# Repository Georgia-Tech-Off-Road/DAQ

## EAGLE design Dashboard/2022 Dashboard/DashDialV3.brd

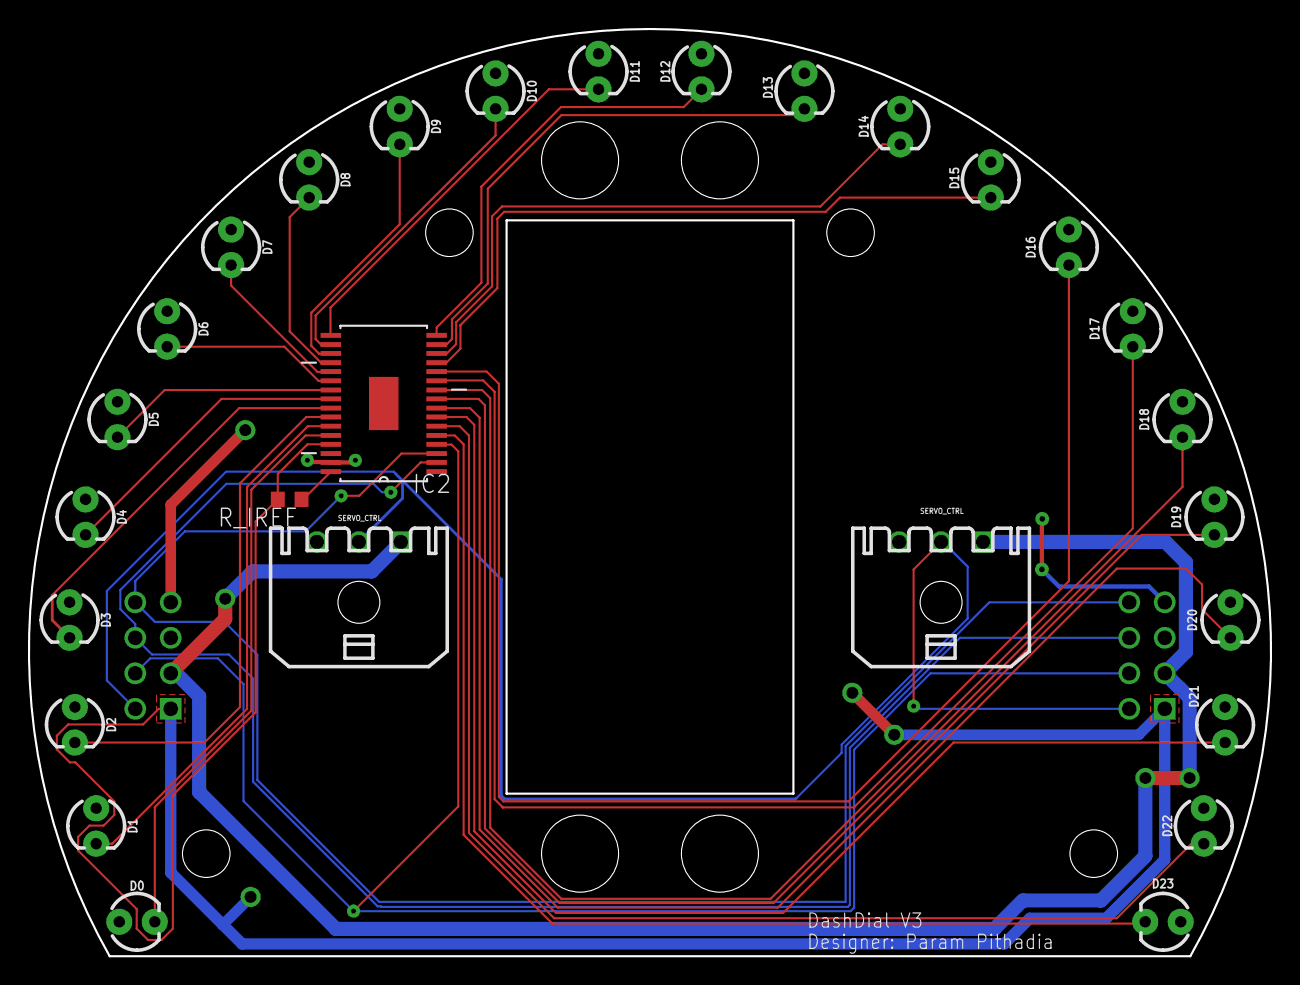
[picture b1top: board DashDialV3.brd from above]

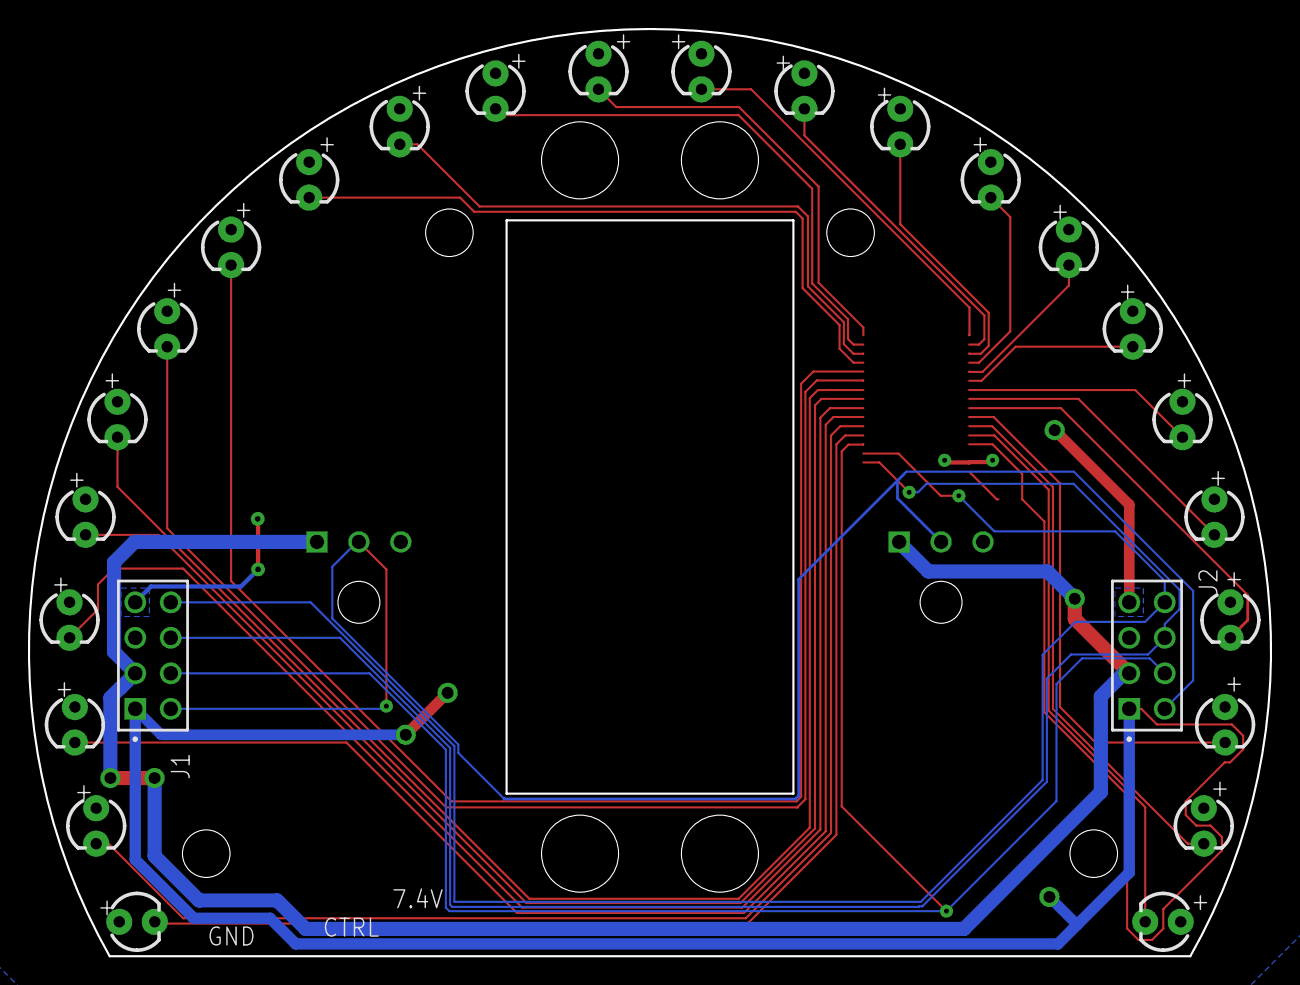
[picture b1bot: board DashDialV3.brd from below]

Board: 2 copper layers, 88.9 x 66.3 mm, 30 parts (2 on the bottom side), 32 nets.

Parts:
D0, D1, D2, D3, D4, D5, D6, D7, D8, D9, D10, D11, D12, D13, D14, D15, D16, D17, D18, D19, D20, D21, D22, D23: LED_3MM
IC2: TLC5952DAP; SOP65P810X120-33N
J1, J2: ESW-104-23-L-D; SAMTEC_ESW-104-23-L-D
R_IREF: 2.4k; R0603
SERVO, SERVO1: 43650-0300

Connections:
3.3V: D0.A, D1.A, D2.A, D3.A, D4.A, D5.A, D6.A, D7.A, D8.A, D9.A, D10.A, D11.A, D12.A, D13.A, D14.A, D15.A, D16.A, D17.A, D18.A, D19.A, D20.A, D21.A, D22.A, D23.A, IC2.31, J1.07, J2.07
7.4V: J1.03, J2.03, SERVO.P$1, SERVO1.P$1
GND: IC2.1, IC2.29, IC2.33, J1.01, J2.01, R_IREF.2, SERVO.P$3, SERVO1.P$3
LAT: IC2.4, J1.04, J2.04
unnamed: IC2.32, R_IREF.1
OUT0: D23.K, IC2.5
OUT1: D22.K, IC2.6
OUT2: D21.K, IC2.7
OUT3: D20.K, IC2.8
OUT4: D19.K, IC2.9
OUT5: D18.K, IC2.10
OUT6: D17.K, IC2.11
OUT7: D16.K, IC2.12
OUT8: D15.K, IC2.13
OUT9: D14.K, IC2.14
OUT10: D13.K, IC2.15
OUT11: D12.K, IC2.16
OUT12: D11.K, IC2.17
OUT13: D10.K, IC2.18
OUT14: D9.K, IC2.19
OUT15: D8.K, IC2.20
OUT16: D7.K, IC2.21
OUT17: D6.K, IC2.22
OUT18: D5.K, IC2.23
OUT19: D4.K, IC2.24
OUT20: D3.K, IC2.25
OUT21: D2.K, IC2.26
OUT22: D1.K, IC2.27
OUT23: D0.K, IC2.28
SCLK: IC2.3, J1.08, J2.08
SERVO_CTRL: J1.02, J2.02, SERVO.P$2, SERVO1.P$2
SIN: IC2.2, J1.06, J2.06

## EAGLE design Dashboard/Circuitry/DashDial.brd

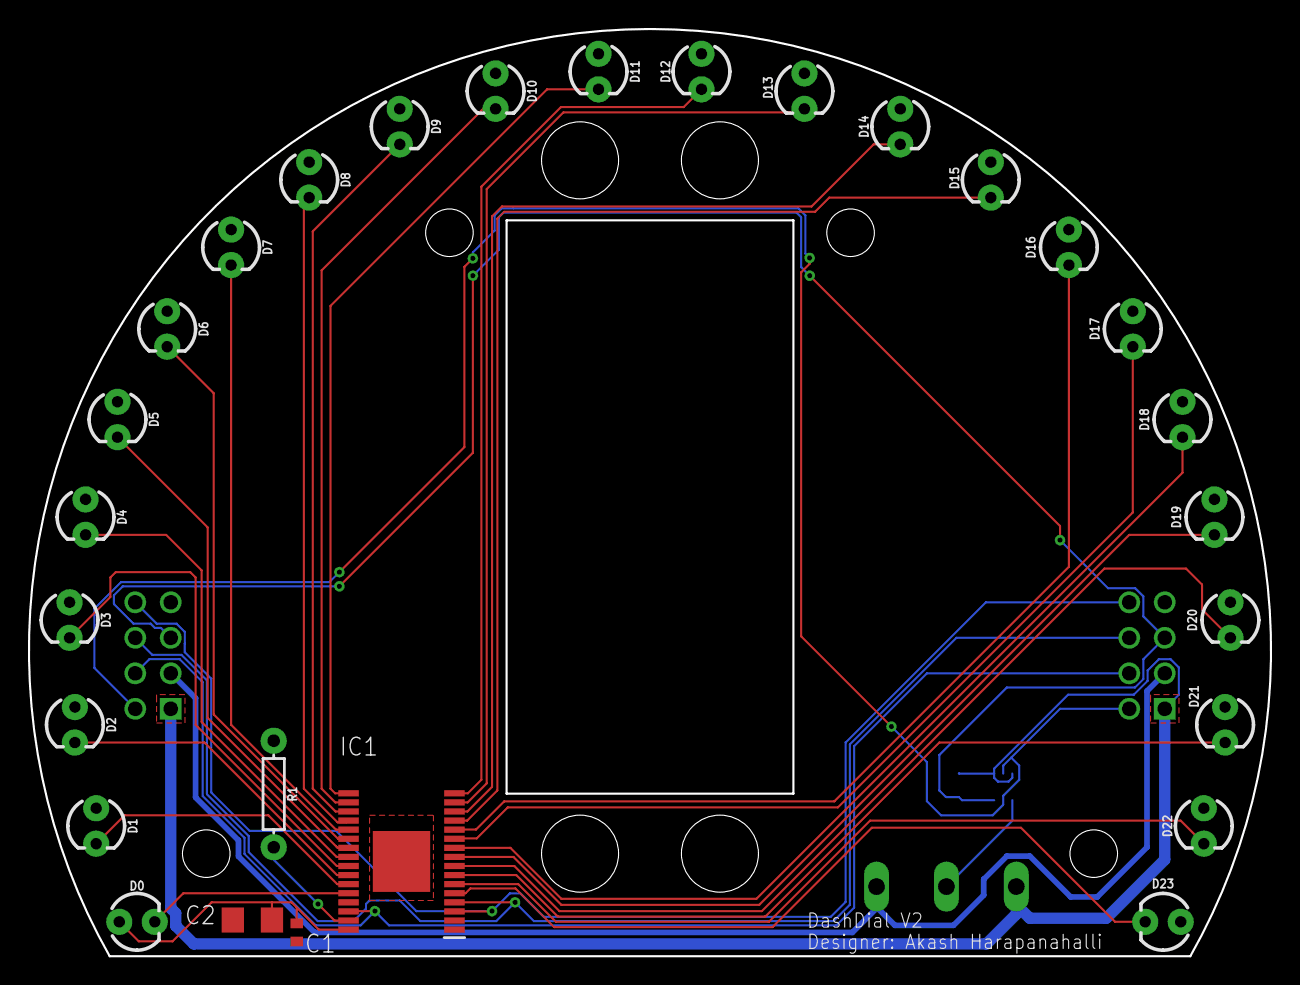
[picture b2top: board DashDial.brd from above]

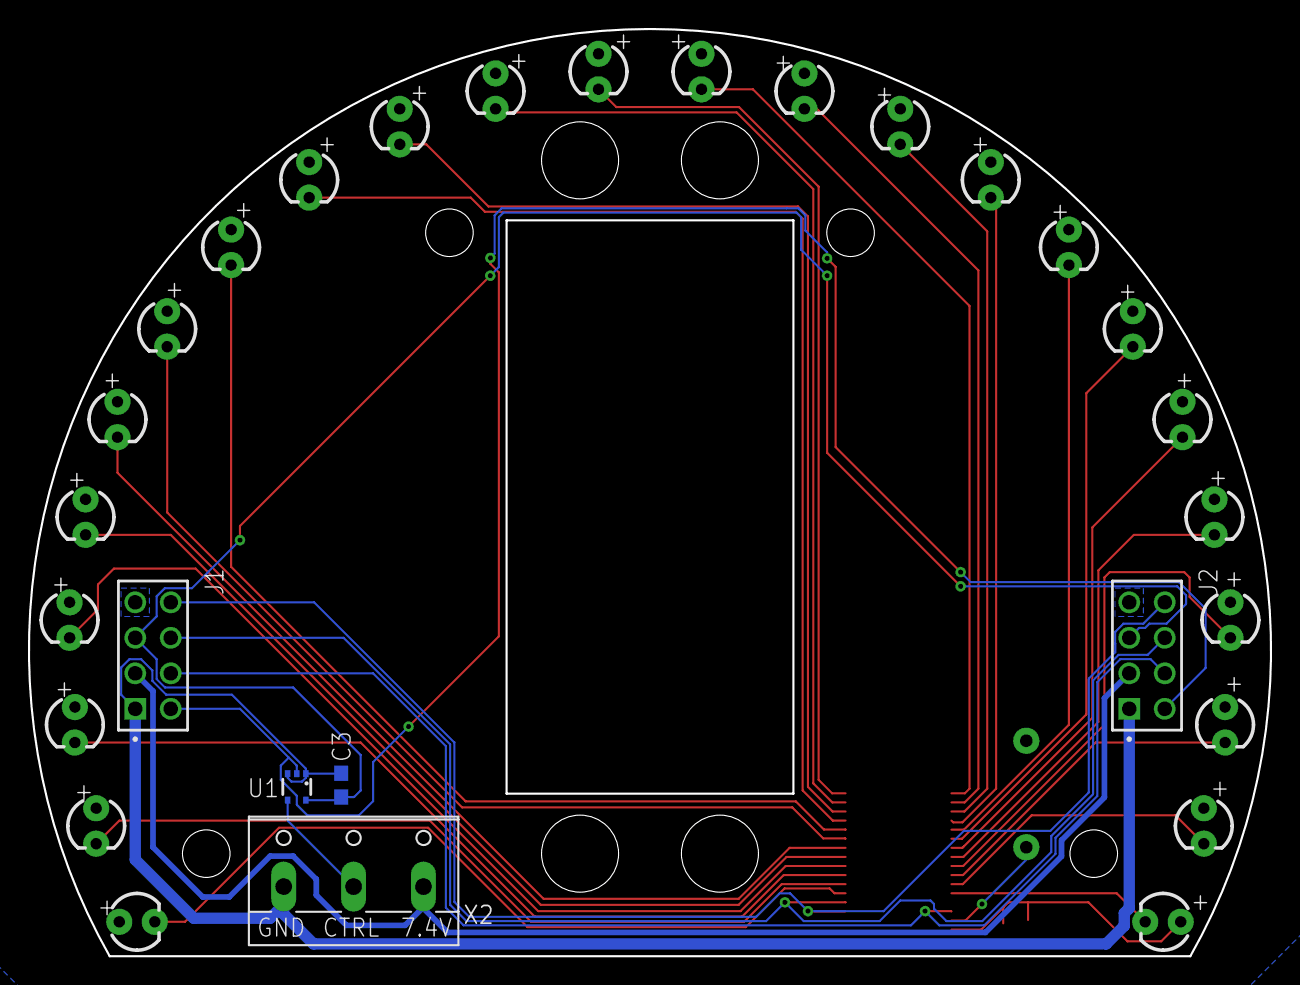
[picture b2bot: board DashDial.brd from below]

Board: 2 copper layers, 88.9 x 66.3 mm, 33 parts (5 on the bottom side), 34 nets.

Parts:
C1: 0.1uF; C0402
C2: 100uF; C1206
C3: 0.1uF; 0603
D0, D1, D2, D3, D4, D5, D6, D7, D8, D9, D10, D11, D12, D13, D14, D15, D16, D17, D18, D19, D20, D21, D22, D23: LED_3MM
IC1: TLC5947DAPR; SOP65P810X120-33N
J1, J2: ESW-104-23-L-D; SAMTEC_ESW-104-23-L-D
R1: 3k; AXIAL-0.3
U1: LOGIC SHIFTER; SOT353
X2: SERVO; W237-103

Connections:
3.3V: C1.2, C2.2, D0.A, D1.A, D2.A, D3.A, D4.A, D5.A, D6.A, D7.A, D8.A, D9.A, D10.A, D11.A, D12.A, D13.A, D14.A, D15.A, D16.A, D17.A, D18.A, D19.A, D20.A, D21.A, D22.A, D23.A, IC1.32, J1.07, J2.07
5V: C3.1, J1.05, J2.05, U1.5
7.4V: J1.03, J2.03, X2.3
GND: C1.1, C2.1, C3.2, IC1.1, IC1.2, IC1.33, J1.01, J2.01, R1.P$1, U1.1, U1.3, X2.1
LAT: IC1.30, J1.04, J2.04
unnamed: U1.4, X2.2
unnamed: IC1.31, R1.P$2
OUT0: D23.K, IC1.5
OUT1: D22.K, IC1.6
OUT2: D21.K, IC1.7
OUT3: D20.K, IC1.8
OUT4: D19.K, IC1.9
OUT5: D18.K, IC1.10
OUT6: D17.K, IC1.11
OUT7: D16.K, IC1.12
OUT8: D15.K, IC1.13
OUT9: D14.K, IC1.14
OUT10: D13.K, IC1.15
OUT11: D12.K, IC1.16
OUT12: D11.K, IC1.17
OUT13: D10.K, IC1.18
OUT14: D9.K, IC1.19
OUT15: D8.K, IC1.20
OUT16: D7.K, IC1.21
OUT17: D6.K, IC1.22
OUT18: D5.K, IC1.23
OUT19: D4.K, IC1.24
OUT20: D3.K, IC1.25
OUT21: D2.K, IC1.26
OUT22: D1.K, IC1.27
OUT23: D0.K, IC1.28
SCLK: IC1.3, J1.08, J2.08
SERVO_CTRL: J1.02, J2.02, U1.2
SIN: IC1.4, J1.06, J2.06

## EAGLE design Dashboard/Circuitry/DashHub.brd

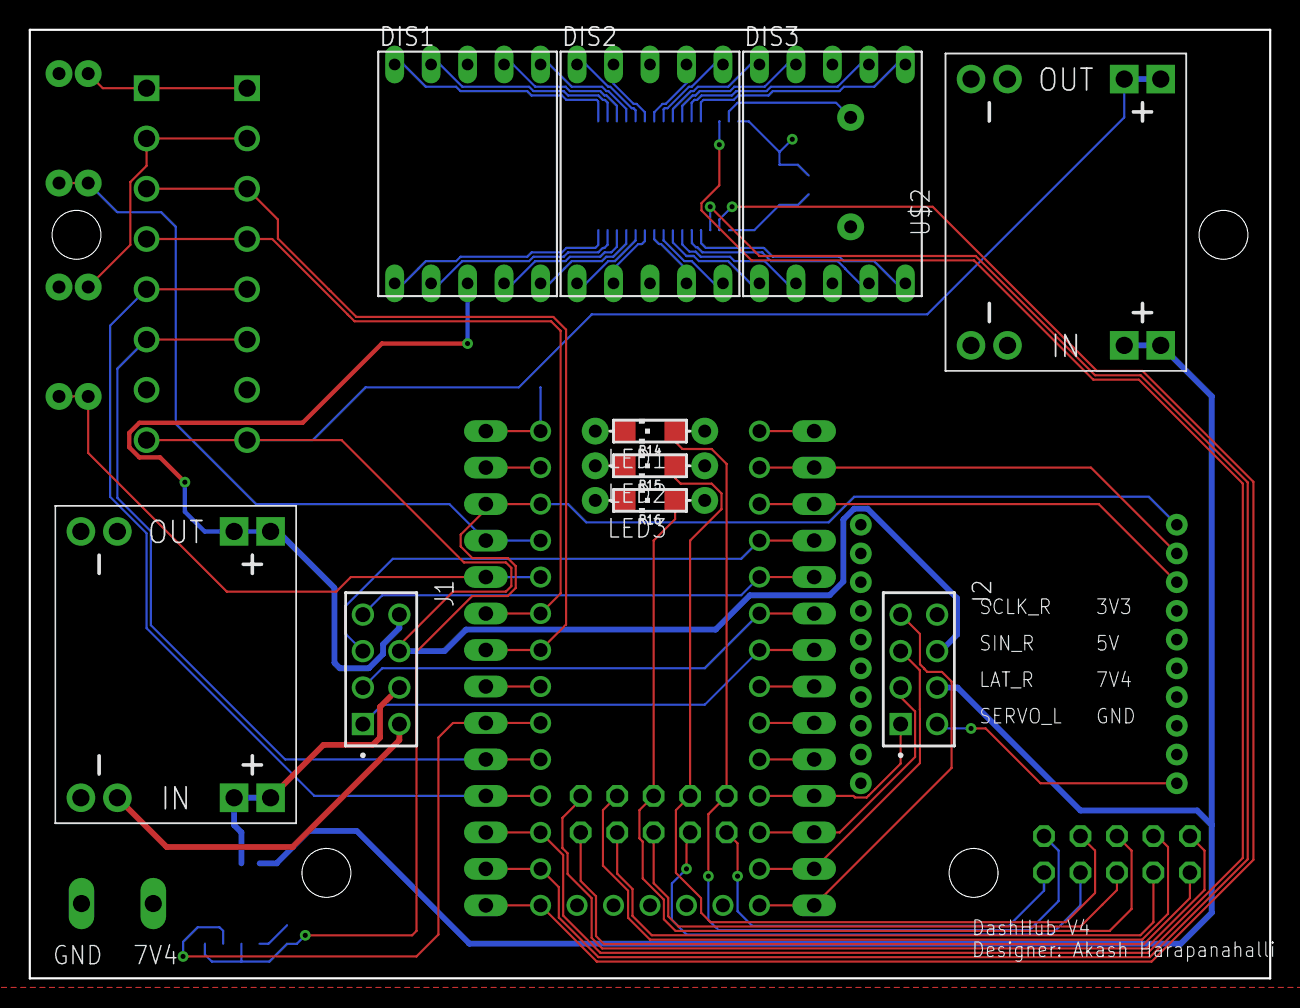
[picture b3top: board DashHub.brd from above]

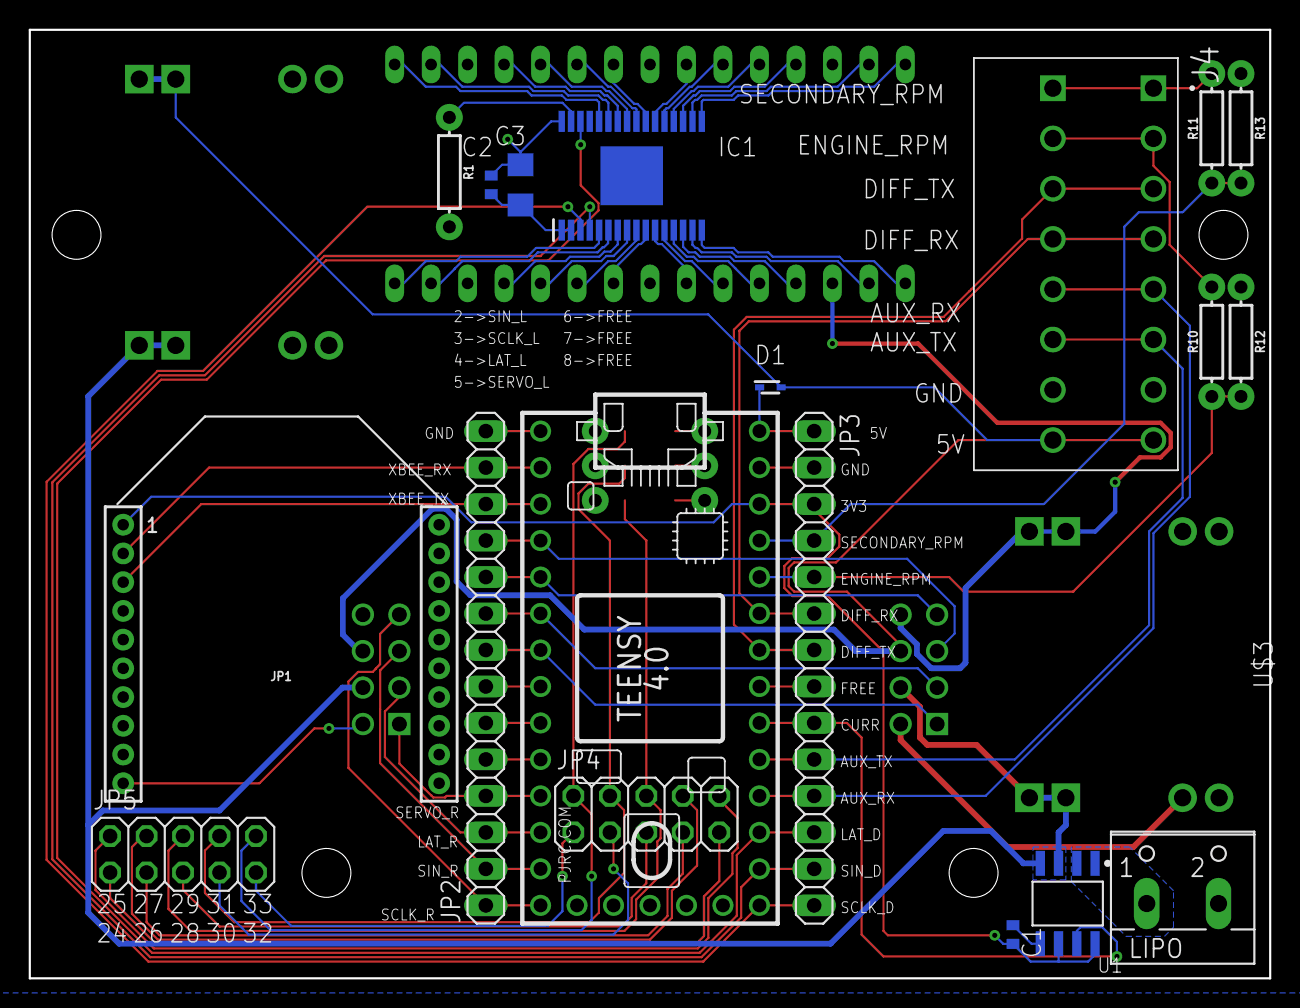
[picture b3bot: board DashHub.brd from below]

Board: 2 copper layers, 86.4 x 66.0 mm, 32 parts (19 on the bottom side), 72 nets.

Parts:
C1, C2: 0.1uF; C0402
C3: 100uF; C1206
D1: RB521S30T1G; SODFL1608X70N
DIS1, DIS2, DIS3: HD-H101; HDSP-M
IC1: TLC5947DAPR; SOP65P810X120-33N
J1: LEFT; SAMTEC_ESW-104-23-L-D
J2: RIGHT; SAMTEC_ESW-104-23-L-D
J4: TBLH10-350-08BK; CUI_TBLH10-350-08BK
JP1: XBEE
JP2, JP3: 1X14
JP4, JP5: 2X05
LED1, LED2, LED3: CHIPLED_1206
LIPO: LIPO; W237-102
R1: 3k; AXIAL-0.3
R10, R11, R12, R13, R14, R15, R16: AXIAL-0.3
U1: ALLEGRO_MICROSYSTEMS_ACS722LLCTR-05AB-TALLEGRO_MI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; ALLEGRO_MICROSYSTEMS_ACS722LLCTR-05AB-T_0
U$1: TEENSY_4.0-BASIC
U$2, U$3: DC-DC-STEP-DOWN-MP1584

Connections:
3.3V_BUCK: C2.2, C3.2, DIS1.3, DIS1.8, DIS2.3, DIS2.8, DIS3.3, DIS3.8, IC1.32, J1.08, J2.08, U$3.OUT+.1, U$3.OUT+.2
3.3V_TEENSY: C1.2, JP1.1, JP3.3, U1.6, U1.8, U$1.3V3_LO
5V: D1.2, J1.06, J2.06, J4.8_A, J4.8_B, U$2.OUT+.1, U$2.OUT+.2
7.4V: J1.04, J2.04, U1.3, U1.4, U$2.IN+.1, U$2.IN+.2, U$3.IN+.1, U$3.IN+.2
24: JP4.9, JP5.1
25: JP4.10, JP5.2
26: JP4.7, JP5.3
27: JP4.8, JP5.4
28: JP4.5, JP5.5
29: JP4.6, JP5.6, LED3.A
30: JP4.3, JP5.7
31: JP4.4, JP5.8, LED2.A
32: JP4.1, JP5.9
33: JP4.2, JP5.10, LED1.A
AUX_RX: J4.5_A, J4.5_B, JP3.11, U$1.16/A2
AUX_TX: J4.6_A, J4.6_B, JP3.10, U$1.17/A3
CURR_SENSE: JP3.9, U1.7, U$1.18/A4/SDA
DIFF_RX: J4.4_A, J4.4_B, JP3.6, U$1.21/A7
DIFF_TX: J4.3_A, J4.3_B, JP3.7, U$1.20/A6
ENGINE_RPM: JP3.5, R10.P$1, R12.P$2, U$1.22/A8
GND: C1.1, C2.1, C3.1, IC1.1, IC1.2, IC1.33, J1.02, J2.02, J4.7_A, J4.7_B, JP1.10, JP2.14, LIPO.2, R1.P$2, R12.P$1, R13.P$1, R14.P$1, R15.P$1, R16.P$1, U1.5, U$1.GND, U$2.IN-.1, U$2.IN-.2, U$2.OUT-.1, U$2.OUT-.2, U$3.IN-.1, U$3.IN-.2, U$3.OUT-.1, U$3.OUT-.2
LAP_RESET: JP2.5, U$1.8
LAT_D: IC1.30, JP3.12, U$1.15/A1
LAT_L: J1.03, JP2.9, U$1.4/CANRX
LAT_R: J2.03, JP2.3, U$1.10/CS
LIPO_IN: LIPO.1, U1.1, U1.2
unnamed: JP2.7, U$1.6
unnamed: D1.1, JP3.1, U$1.VIN
unnamed: JP2.6, U$1.7
unnamed: JP3.8, U$1.19/A5/SCL
unnamed: LED1.C, R14.P$2
unnamed: LED2.C, R15.P$2
unnamed: LED3.C, R16.P$2
unnamed: JP3.2, U$1.GND2
unnamed: J4.2_A, J4.2_B, R10.P$2
unnamed: J4.1_A, J4.1_B, R11.P$2
unnamed: IC1.31, R1.P$1
OUT0: DIS3.5, IC1.5
OUT1: DIS3.4, IC1.6
OUT2: DIS3.2, IC1.7
OUT3: DIS3.1, IC1.8
OUT4: DIS2.5, IC1.9
OUT5: DIS2.4, IC1.10
OUT6: DIS2.2, IC1.11
OUT7: DIS2.1, IC1.12
OUT8: DIS1.5, IC1.13
OUT9: DIS1.4, IC1.14
OUT10: DIS1.2, IC1.15
OUT11: DIS1.1, IC1.16
OUT12: DIS1.10, IC1.17
OUT13: DIS1.9, IC1.18
OUT14: DIS1.7, IC1.19
OUT15: DIS1.6, IC1.20
OUT16: DIS2.10, IC1.21
OUT17: DIS2.9, IC1.22
OUT18: DIS2.7, IC1.23
OUT19: DIS2.6, IC1.24
OUT20: DIS3.10, IC1.25
OUT21: DIS3.9, IC1.26
OUT22: DIS3.7, IC1.27
OUT23: DIS3.6, IC1.28
SCLK_D: IC1.3, JP3.14, U$1.13/SCK
SCLK_L: J1.07, JP2.10, U$1.3/CANTX
SCLK_R: J2.07, JP2.1, U$1.12/MISO
SECONDARY_RPM: JP3.4, R11.P$1, R13.P$2, U$1.23/A9
SERVO_L: J1.01, JP2.8, U$1.5
SERVO_R: J2.01, JP2.4, U$1.9/CS
SIN_D: IC1.4, JP3.13, U$1.14/A0
SIN_L: J1.05, JP2.11, U$1.2
SIN_R: J2.05, JP2.2, U$1.11/MOSI
XBEE_RX: JP1.2, JP2.13, U$1.0/RX
XBEE_TX: JP1.3, JP2.12, U$1.1/TX

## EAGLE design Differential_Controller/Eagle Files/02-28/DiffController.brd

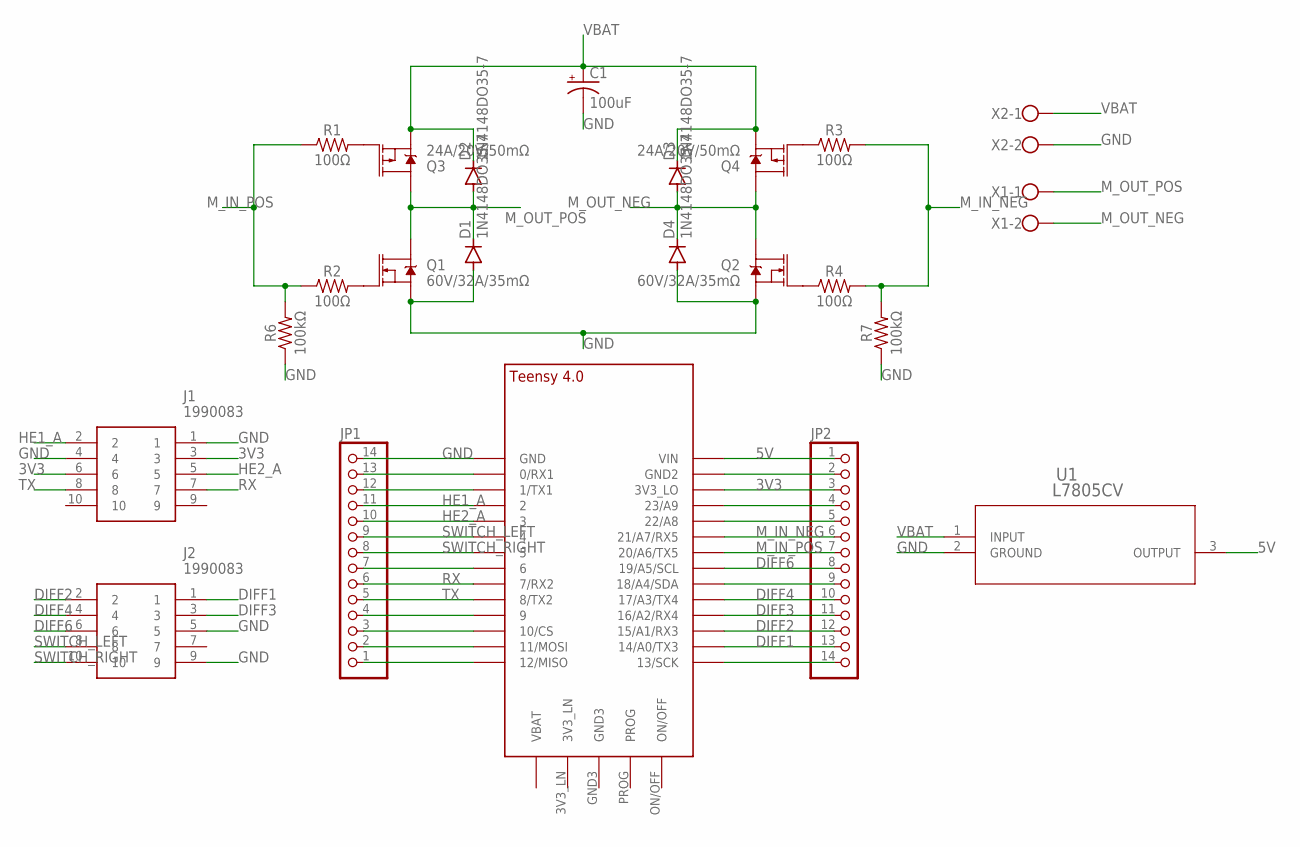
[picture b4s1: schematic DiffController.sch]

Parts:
C1: 100uF; CPOL-RADIAL-2.5MM-6.5MM
D1, D2, D3, D4: 1N4148DO35-7; DO35-7
J1, J2: 1990083
JP1, JP2: PINHD-1X14; 1X14
Q1, Q2: 60V/32A/35mΩ; TO220V
Q3, Q4: 24A/20V/50mΩ; TO220V
R1, R2, R3, R4: 100Ω; AXIAL-0.3
R6, R7: 100kΩ; AXIAL-0.3
U1: L7805CV; TO-220_STM
U$2: TEENSY_4.0_EXPANDED_1
X1, X2: W237-102

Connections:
3V3: J1.3, J1.6, JP2.3, U$2.3V3_LO
5V: JP2.1, U1.3 (OUTPUT), U$2.VIN
DIFF1: J2.1, JP2.13, U$2.14/A0 (14/A0/TX3)
DIFF2: J2.2, JP2.12, U$2.15/A1 (15/A1/RX3)
DIFF3: J2.3, JP2.11, U$2.16/A2 (16/A2/RX4)
DIFF4: J2.4, JP2.10, U$2.17/A3 (17/A3/TX4)
DIFF6: J2.6, JP2.8, U$2.19/A5/SCL
GND: C1.2 (-), D1.A, D4.A, J1.1, J1.4, J2.5, J2.9, JP1.14, Q1.3 (S), Q2.3 (S), R6.P$1 (1), R7.P$1 (1), U1.2 (GROUND), U$2.GND, X2.2
HE1_A: J1.2, JP1.11, U$2.2
HE2_A: J1.5, JP1.10, U$2.3/CANTX (3)
M_IN_NEG: JP2.6, R3.P$2 (2), R4.P$2 (2), R7.P$2 (2), U$2.21/A7 (21/A7/RX5)
M_IN_POS: JP2.7, R1.P$1 (1), R2.P$1 (1), R6.P$2 (2), U$2.20/A6 (20/A6/TX5)
M_OUT_NEG: D3.A, D4.C, Q2.2 (D), Q4.2 (D), X1.2
M_OUT_POS: D1.C, D2.A, Q1.2 (D), Q3.2 (D), X1.1
unnamed: JP2.9, U$2.18/A4/SDA
unnamed: JP2.4, U$2.23/A9
unnamed: JP1.13, U$2.0/RX (0/RX1)
unnamed: JP1.12, U$2.1/TX (1/TX1)
unnamed: JP2.2, U$2.GND2
unnamed: JP1.4, U$2.9/CS (9)
unnamed: JP1.3, U$2.10/CS
unnamed: JP1.2, U$2.11/MOSI
unnamed: JP1.1, U$2.12/MISO
unnamed: JP2.14, U$2.13/SCK
unnamed: JP1.7, U$2.6
unnamed: JP2.5, U$2.22/A8
unnamed: Q1.1 (G), R2.P$2 (2)
unnamed: Q2.1 (G), R4.P$1 (1)
unnamed: Q3.1 (G), R1.P$2 (2)
unnamed: Q4.1 (G), R3.P$1 (1)
RX: J1.7, JP1.6, U$2.7 (7/RX2)
SWITCH_LEFT: J2.8, JP1.9, U$2.4/CANRX (4)
SWITCH_RIGHT: J2.10, JP1.8, U$2.5
TX: J1.8, JP1.5, U$2.8 (8/TX2)
VBAT: C1.1 (+), D2.C, D3.C, Q3.3 (S), Q4.3 (S), U1.1 (INPUT), X2.1

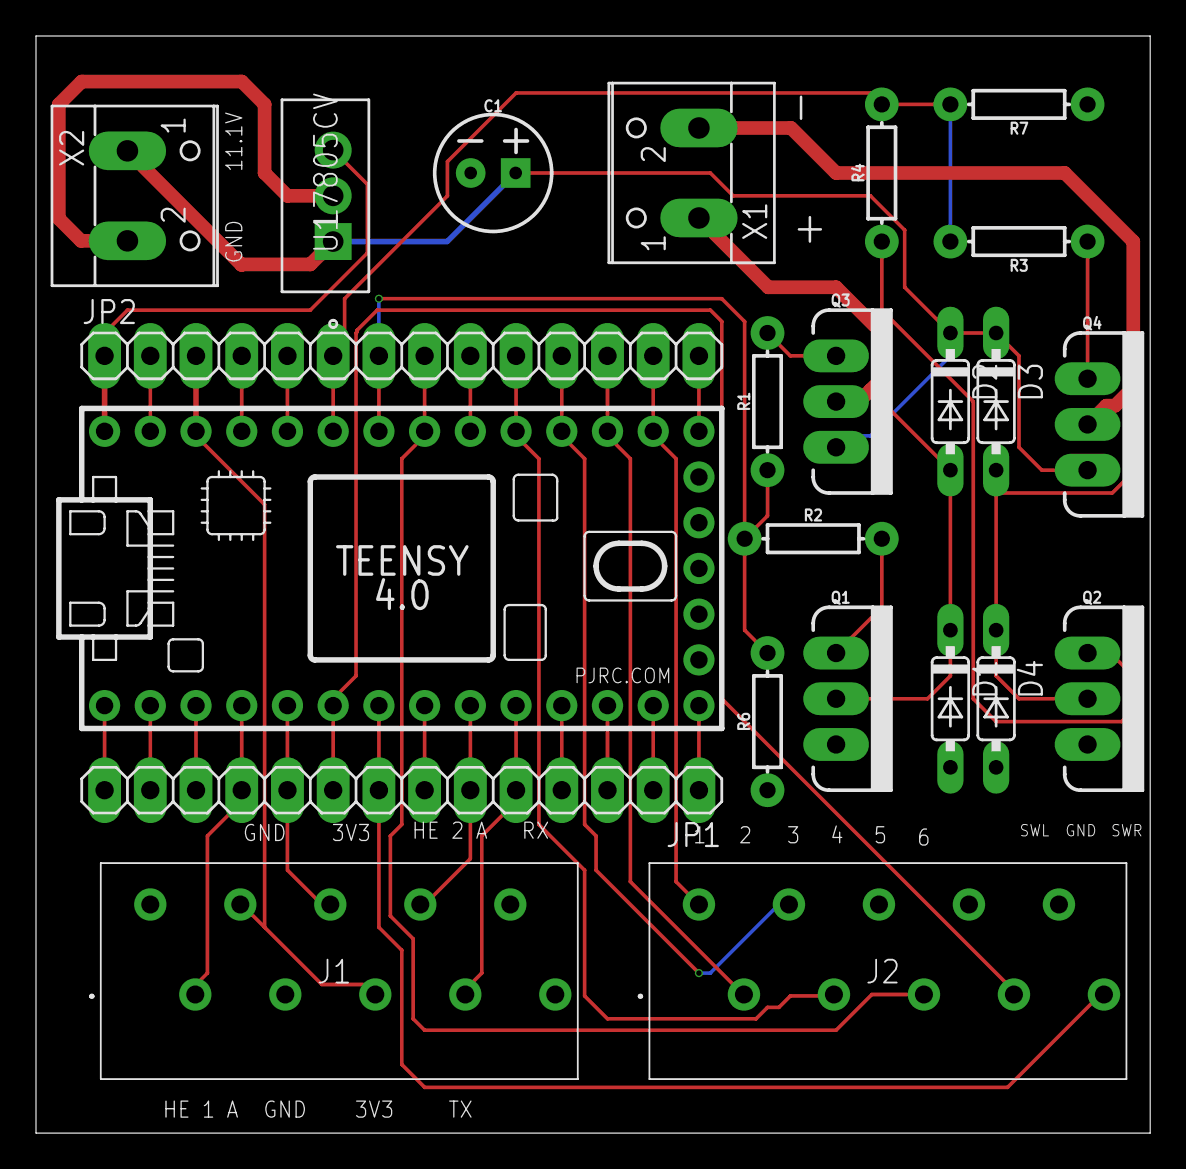
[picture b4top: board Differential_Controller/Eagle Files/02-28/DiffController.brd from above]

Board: 2 copper layers, 61.9 x 60.9 mm, 23 parts (0 on the bottom side), 35 nets.

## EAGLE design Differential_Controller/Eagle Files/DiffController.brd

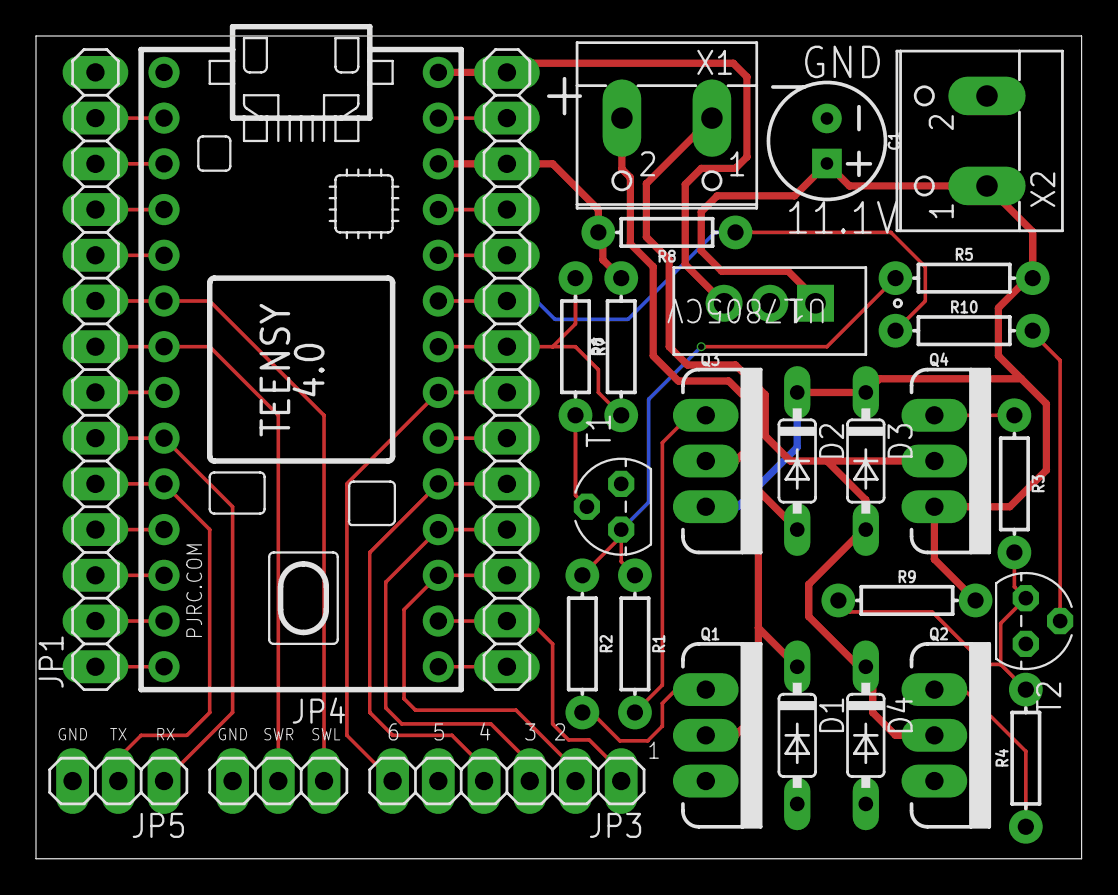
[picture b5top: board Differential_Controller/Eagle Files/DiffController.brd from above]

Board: 2 copper layers, 58.1 x 45.7 mm, 30 parts (0 on the bottom side), 39 nets.

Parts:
C1: 100uF; CPOL-RADIAL-2.5MM-6.5MM
D1, D2, D3, D4: 1N4148DO35-7; DO35-7
JP1, JP2: 1X14
JP3: 1X06
JP4, JP5: 1X03
Q1, Q2: 60V/32A/35mΩ; TO220V
Q3, Q4: 24A/20V/50mΩ; TO220V
R1, R2, R3, R4: 100Ω; AXIAL-0.3
R5, R6, R8, R9: 10kΩ; AXIAL-0.3
R7, R10: 1kΩ; AXIAL-0.3
T1, T2: BC337; TO92
U1: L7805CV; TO-220_STM
U$1: TEENSY_4.0_SIMPLE
X1, X2: W237-102

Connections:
3V3: JP2.3, R6.P$2, R8.P$2, U$1.3V3_LO
5V: JP2.1, U1.3, U$1.VIN
DIFF1: JP2.13, JP3.1, U$1.14/A0
DIFF2: JP2.12, JP3.2, U$1.15/A1
DIFF3: JP2.11, JP3.3, U$1.16/A2
DIFF4: JP2.10, JP3.4, U$1.17/A3
DIFF6: JP2.8, JP3.6, U$1.19/A5/SCL
GND: C1.2, D1.A, D4.A, JP1.14, JP3.5, JP4.3, JP5.3, Q1.3, Q2.3, T1.1, T2.1, U1.2, U$1.GND, X2.2
M_IN_NEG: JP2.6, R8.P$1, R10.P$1, U$1.21/A7
M_IN_POS: JP2.7, R6.P$1, R7.P$1, U$1.20/A6
M_OUT_NEG: D3.A, D4.C, Q2.2, Q4.2, X1.1
M_OUT_POS: D1.C, D2.A, Q1.2, Q3.2, X1.2
unnamed: JP2.9, U$1.18/A4/SDA
unnamed: JP2.4, U$1.23/A9
unnamed: JP1.13, U$1.0/RX
unnamed: JP1.12, U$1.1/TX
unnamed: JP2.2, U$1.GND2
unnamed: JP1.4, U$1.9/CS
unnamed: JP1.3, U$1.10/CS
unnamed: JP1.2, U$1.11/MOSI
unnamed: JP1.1, U$1.12/MISO
unnamed: JP2.14, U$1.13/SCK
unnamed: JP1.7, U$1.6
unnamed: JP2.5, U$1.22/A8
unnamed: Q1.1, R2.P$2
unnamed: Q2.1, R4.P$1
unnamed: Q3.1, R1.P$2
unnamed: Q4.1, R3.P$1
unnamed: R3.P$2, R4.P$2, R9.P$1, T2.3
unnamed: R7.P$2, T1.2
unnamed: R1.P$1, R2.P$1, R5.P$1, T1.3
unnamed: R10.P$2, T2.2
unnamed: JP1.11, U$1.2
unnamed: JP1.10, U$1.3/CANTX
RX: JP1.6, JP5.1, U$1.7
SWITCH_LEFT: JP1.9, JP4.1, U$1.4/CANRX
SWITCH_RIGHT: JP1.8, JP4.2, U$1.5
TX: JP1.5, JP5.2, U$1.8
VBAT: C1.1, D2.C, D3.C, Q3.3, Q4.3, R5.P$2, R9.P$2, U1.1, X2.1

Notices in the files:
parts and their libraries:
SparkFun-LED: Licensing: Creative Commons ShareAlike 4.0 International - https://creativecommons.org/licenses/by-sa/4.0
diy-modules: Released under the Creative Commons Attribution 4.0 International License: http://creativecommons.org/licenses/by/4.0
